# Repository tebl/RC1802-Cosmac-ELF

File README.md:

# RC1802 Cosmac ELF
There are two ways you can get involved with computers on the nonprofessional level. You can buy one of several reasonably priced hobby computers, with all the added bells and whistles you'd ever want. On the other hand, you can build your own inexpensive system from scratch.

That was rougly the start of the iconic Cosmac ELF-computers history, it was august 1976 and Popular Electronics magazine had just printed the first in a series of tutorials on how everyone could build their own computers using only common parts and the new 1802 processor from RCA.

Back in 2018 this computer still continues to fascinate... several people, definitively me among them so thanks to the glory of the Internet we can still read the original articles online at [American Radio History.Com](https://www.americanradiohistory.com/Popular-Electronics-Guide.htm):
- [1976-08 Build the Cosmac "ELF" Part 1](https://www.americanradiohistory.com/Archive-Poptronics/70s/1976/Poptronics-1976-08.pdf)
- [1976-09 Build the Cosmac "ELF" Part 2](https://www.americanradiohistory.com/Archive-Poptronics/70s/1976/Poptronics-1976-09.pdf)
- [1977-03 How to expand memory, plus more programs](https://www.americanradiohistory.com/Archive-Poptronics/70s/1977/Poptronics-1977-03.pdf)
- [1977-07 Build the PIXIE Graphic Display](https://www.americanradiohistory.com/Archive-Poptronics/70s/1977/Poptronics-1977-07.pdf)

Thankfully someone already made a version of the computer that's available in kit form and in all ways a fantastic piece of kit, that kit is [Lee Hart's 1802 Membership card](http://www.sunrise-ev.com/membershipcard.htm). If you want the whole package, that's the one to get! So, why on earth did I make another one?

Because I wanted the experience on creating one the old fashioned way, also it had a lot of bits and bobs I never could figure out how worked... I don't have a degree in electronics, so every attempt to explain it to me has so far failed so this was my attempt to reduce all the things I didn't understand to just the minimal number of things I don't understand, yet somehow the thing actually works after only five revisions! There were some stupid mistakes done on the first ones, so let's not dig too far back in the commit logs as I'm easily embarrassed.

While the first version had 256 bytes of RAM, this one supports a whopping 64K of addressable memory in the form of two slots that'll take either RAM or ROM! Should be more than enough for anyone, even if you've got ninja skills at toggling in data! Other added features includes extra blinking LEDs, a lot of them!

## Errata
- UI module revision D had issues where some traces were moved without doing ground plane refill, some lines may appear shorted because of it is. Recommended to replace UI module, but can be cut and rewired according to updated board - see [before](https://github.com/tebl/RC1802-Cosmac-ELF/raw/master/Gallery/1802_ui_d1.PNG) and [after](https://github.com/tebl/RC1802-Cosmac-ELF/raw/master/Gallery/1802_ui_d2.PNG) for reference.
- CPU module revisions D through E had a fault relating to connection of 1802 pin 37 (DMA OUT), mainly that it was never actually connected to anything. Revision F fixes this issue, but you can fix earlier revisions by adding a wire between the bottom of resistor R2 and 1802 pin 37.
- CPU module revision D had **a short** between **GND and VCC**! Later revisions do not have this issue, but if you have this version of the board: please remove pin 40 of the UI connector (top left pin) before attempting to power it up!

## Modules
In order to create a working RC1802 Cosmac ELF computer you will need the following set of modules:
- [CPU Board](https://github.com/tebl/RC1802-Cosmac-ELF/tree/master/RC1802%20CPU) ([order](https://www.pcbway.com/project/shareproject/RC1802_Cosmac_ELF__CPU_module_revision_E_.html?inviteid=88707))
- [User Interface](https://github.com/tebl/RC1802-Cosmac-ELF/tree/master/RC1802%20UI) ([order](https://www.pcbway.com/project/shareproject/RC1802_Cosmac_ELF__UI_module_revision_E_.html?inviteid=88707))

Optional modules:
- [Backplane](https://github.com/tebl/RC6502-Apple-1-Replica/tree/master/RC6502%20Backplane) ([order](https://www.pcbway.com/project/shareproject/RC6502_Apple_1_Replica__Backplane_module_revision_A_.html?inviteid=88707))

If you would like to have a copy of one or more modules, what you'll need to do is zip up the contents of the export directory for each module and give that to your favourite PCB fabrication plant. Personally I prefer to use [PCBWay](https://www.pcbway.com/setinvite.aspx?inviteid=88707), each module is only 5$ each and new accounts even get the first one free! Please use the supplied link when signing up to help me support this project, I'll get a small discount on future orders and hopefully I can afford to keep developing new and exciting modules. Even easier, you can just click the orderring-url after each of the modules - that way you'll get something that works on the first try, and you'll support me in a small way for using the URL!

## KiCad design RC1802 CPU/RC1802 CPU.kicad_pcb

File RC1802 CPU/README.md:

# RC1802 CPU Module

Of the two main modules needed for the RC1802 Cosmac ELF computer, this is the main board that includes the RCA 1802 processor along with any RAM and ROM you want. In other words this is the brains of the whole operation! In theory this board by itself should be able to function by itself though the validity of this claim is still lacking some actual testing.

# Schematic
The supplied KiCad files should be sufficient as both a schematic and as a  starting point for ordering PCBs (basically you could just zip the contents of the export folder and upload that on a fabrication site), the schematic is also available in [PDF-format](https://github.com/tebl/RC1802-Cosmac-ELF/raw/master/RC1802%20CPU/export/RC1802%20CPU.pdf) and this is what you'll need to print and work your way through this things don't work as expected after assembly.

# BOM
Most parts should be easy to get a hold of from your favourite local electronic component shop though you might have to consider other sources for the older parts such as the CPU and memory. Personally I bought most components with free shipping from China via AliExpress - prices will vary, but I found everything in larger quantities than needed for the cost of a few cups of fancy coffee! You don't need the newest and fastest components, after all it's going into a 70s-era computer so don't go overboard unless you want to (you can replace 74LS ICs with 74HCT or 74ALS if you want something newer). Most components have been produced by various manufacturers, these mostly do the same thing without any relevant differences though the choice of CPU and PIA could lead to incompatibilities so I've specified the ones I've had success with (probably also the cheapest ones available).

Some vendors will have the same ICs in different form factors, the ones you want will often be specified as being in the form of a DIP/PDIP package. Usually you'll want sockets for each of the ICs as well, a bag of assorted sockets should be easily available without setting you back more than a couple bucks. With the sockets in place, you don't need to dread having to remove an IC later, this leads to easier fault finding and you can even "borrow" them for other projects later! For the pin headers, both male and female - if you can't find the exact pin count, just buy the longer versions and snip off the parts you don't need.

Values in parenthesis is the component amounts that could be considered optional.

| Reference    | Item                                  | Count |
| ------------ | ------------------------------------- | ----- |
| PCB          | Fabricate using Gerber files ([order](https://www.pcbway.com/project/shareproject/RC1802_Cosmac_ELF__CPU_module_revision_D_.html))  |     1 |
| C1-C6        | 100nF ceramic capacitor               |     6 |
| D1-D8        | 5mm LED (assorted colours)            |   (8) |
| J5           | 1x39 right-angle pin header           |   (1) |
| J6           | 2x20 pin header                       |     1 |
| J7           | 3 pin DC barrel connector             |     1 |
| J8           | 1x05 pin header                       |     1 |
| J9           | 1x04 pin header                       |     1 |
| JP2-JP6      | 1x03 pin header                       |     5 |
| R1-R7        | 47k ohm resistor                      |     7 |
| R8-R15       | 220 ohm resistor                      |   (8) |
| U1           | 74LS04 DIP-14                         |     1 |
| U2           | CDP1802 CPU DIP-40                    |     1 |
| U3           | 74LS240 DIP-20                        |   (1) |
| U4           | 74LS373 DIP-20                        |     1 |
| U5-U6        | 62256 Static RAM DIP-28               | 1 (1) |
| X1           | 1.000Mhz TTL Oscillator, (DIP 14)     |     1 |

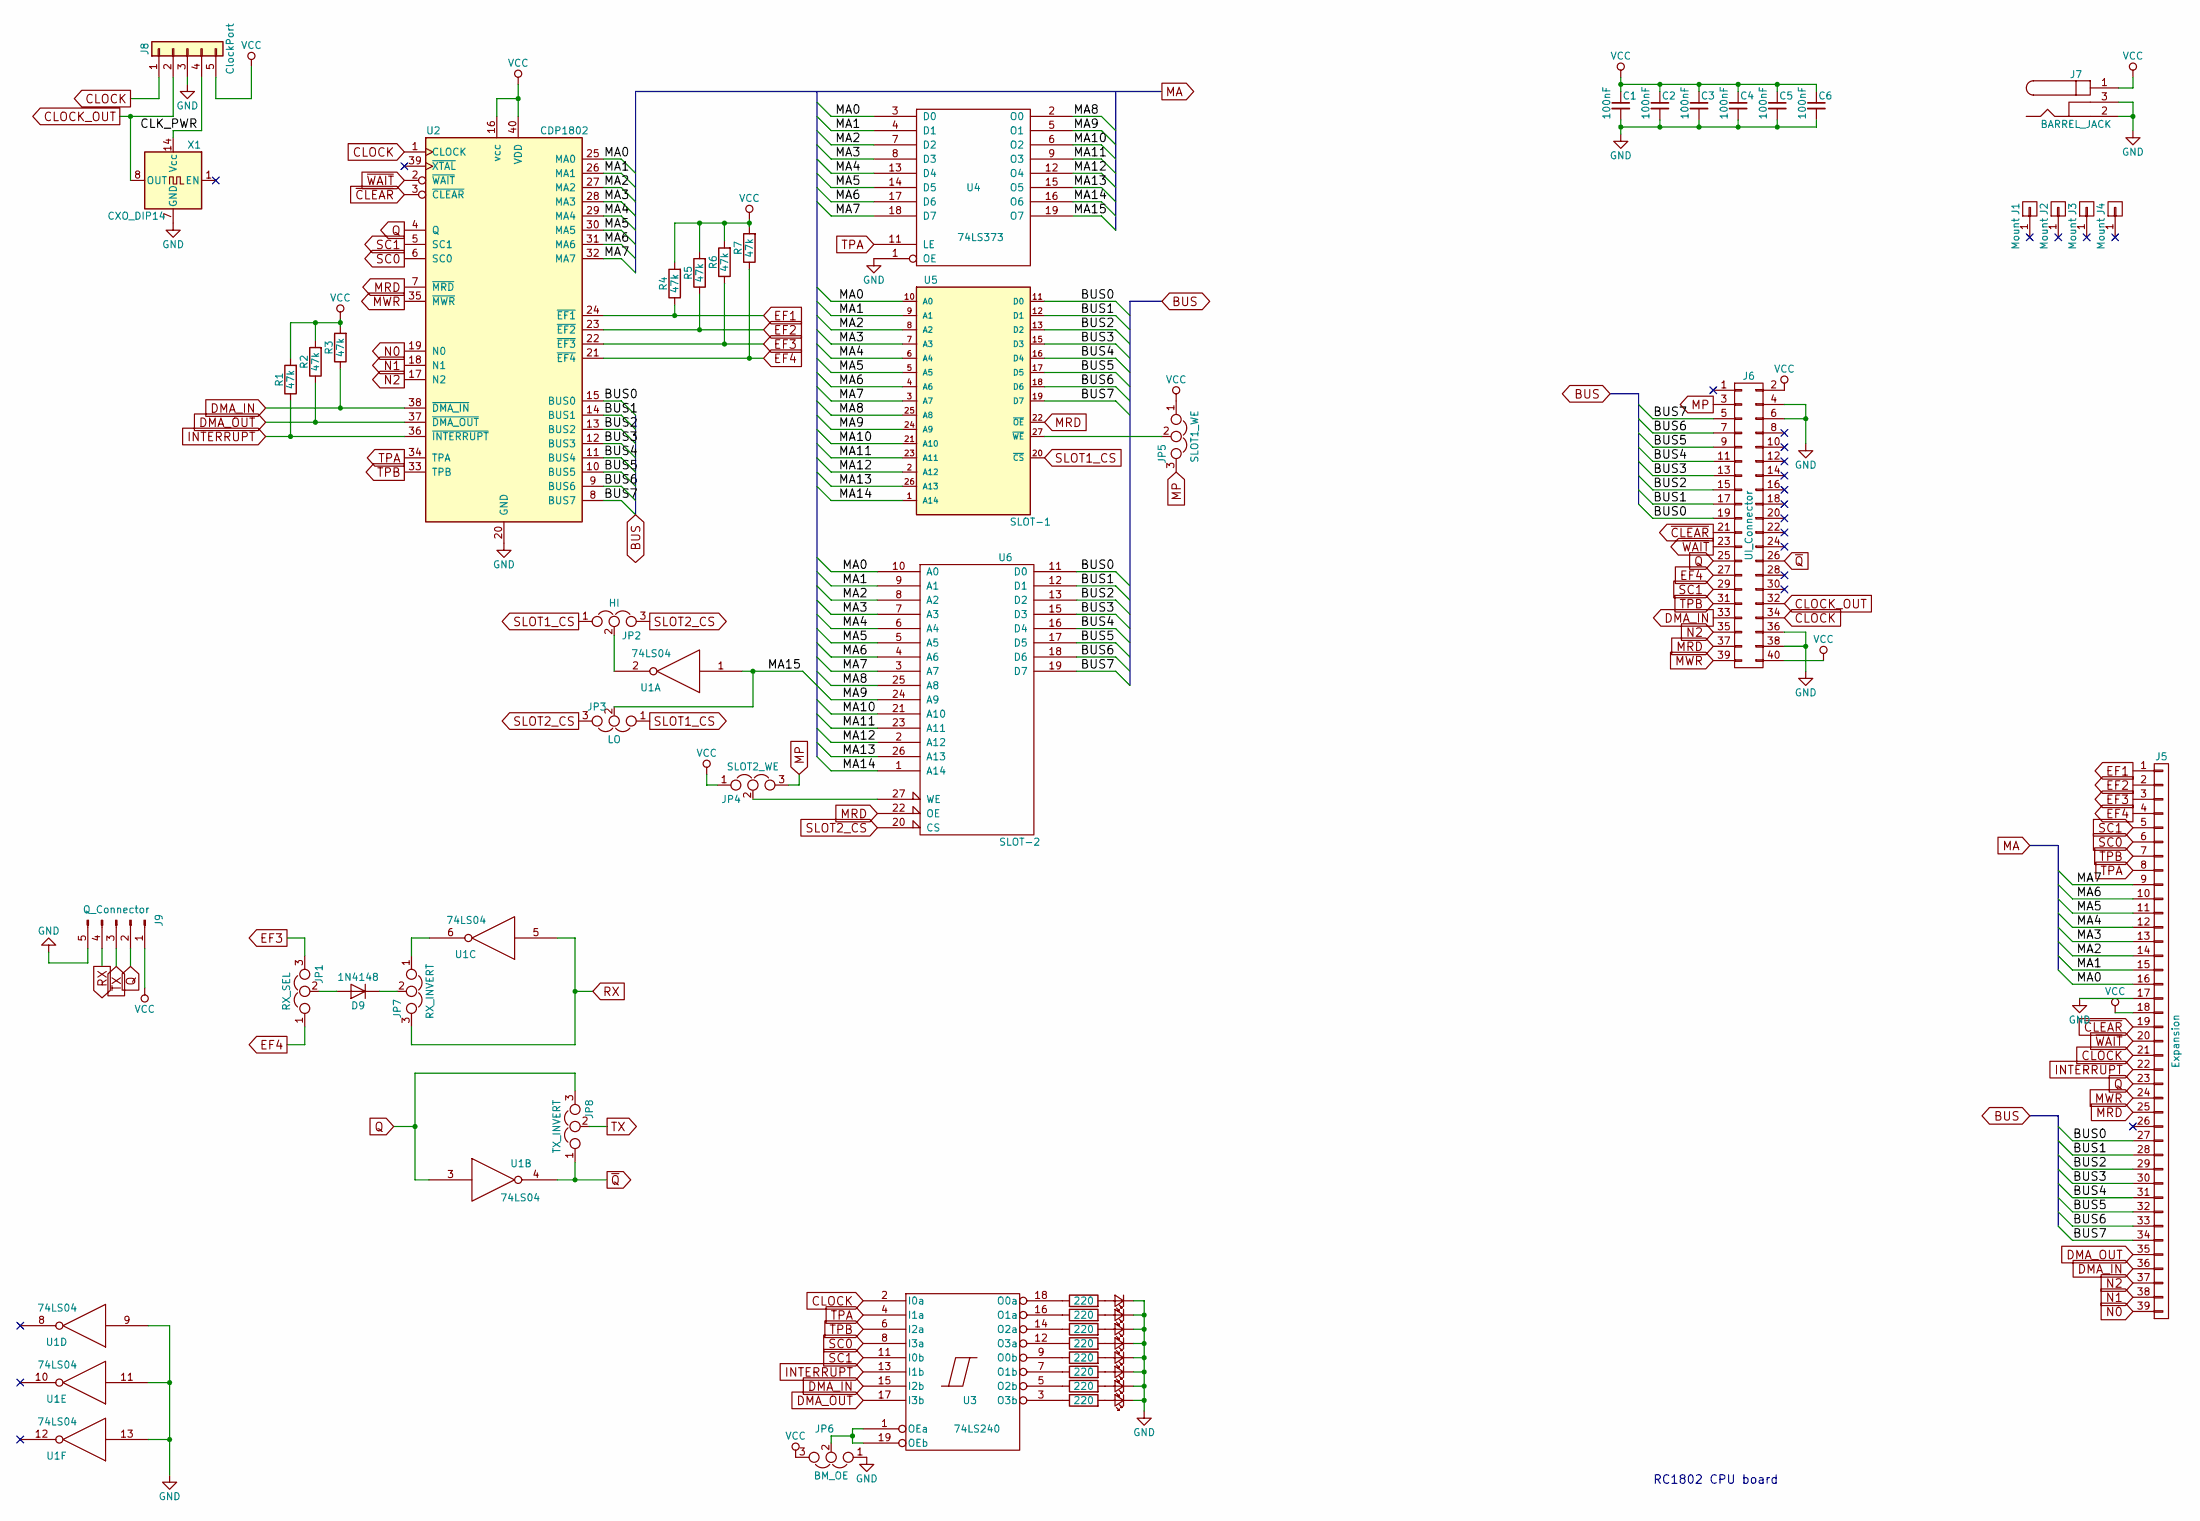
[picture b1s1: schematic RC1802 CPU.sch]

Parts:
C1, C2, C3, C4, C5, C6: 100nF; C_Disc_D4.7mm_W2.5mm_P5.00mm
D1, D2, D3, D4, D5, D6, D7, D8: LED_Small; LED_D5.0mm
D9: 1N4148; D_DO-35_SOD27_P7.62mm_Horizontal
J1, J2, J3, J4: Mount; 1pin
J5: Expansion; Pin_Header_Angled_1x39_Pitch2.54mm
J6: UI_Connector; Pin_Header_Straight_2x20_Pitch2.54mm
J7: BARREL_JACK
J8: ClockPort; Pin_Header_Straight_1x05_Pitch2.54mm
J9: Q_Connector; Pin_Header_Angled_1x05_Pitch2.54mm
JP1: RX_SEL; Pin_Header_Straight_1x03_Pitch2.54mm
JP2: HI; Pin_Header_Straight_1x03_Pitch2.54mm
JP3: LO; Pin_Header_Straight_1x03_Pitch2.54mm
JP4: SLOT2_WE; Pin_Header_Straight_1x03_Pitch2.54mm
JP5: SLOT1_WE; Pin_Header_Straight_1x03_Pitch2.54mm
JP6: BM_OE; Pin_Header_Straight_1x03_Pitch2.54mm
JP7: RX_INVERT; Pin_Header_Straight_1x03_Pitch2.54mm
JP8: TX_INVERT; Pin_Header_Straight_1x03_Pitch2.54mm
R1, R2, R3, R4, R5, R6, R7: 47k; R_Axial_DIN0207_L6.3mm_D2.5mm_P10.16mm_Horizontal
R8, R9, R10, R11, R12, R13, R14, R15: 220; R_Axial_DIN0207_L6.3mm_D2.5mm_P10.16mm_Horizontal
U1: 74LS04; DIP-14_W7.62mm_Socket
U2: CDP1802; DIP-40_W15.24mm_Socket
U3: 74LS240; DIP-20_W7.62mm_Socket
U4: 74LS373; DIP-20_W7.62mm_Socket
U5: SLOT-1; DIP-28_W15.24mm_Socket
U6: SLOT-2; DIP-28_W15.24mm_Socket
X1: CXO_DIP14; Oscillator_DIP-14

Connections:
/BUS0: J5.27, J6.19, U2.15 (BUS0), U5.11 (D0), U6.11 (D0)
/BUS1: J5.28, J6.17, U2.14 (BUS1), U5.12 (D1), U6.12 (D1)
/BUS2: J5.29, J6.15, U2.13 (BUS2), U5.13 (D2), U6.13 (D2)
/BUS3: J5.30, J6.13, U2.12 (BUS3), U5.15 (D3), U6.15 (D3)
/BUS4: J5.31, J6.11, U2.11 (BUS4), U5.16 (D4), U6.16 (D4)
/BUS5: J5.32, J6.9, U2.10 (BUS5), U5.17 (D5), U6.17 (D5)
/BUS6: J5.33, J6.7, U2.9 (BUS6), U5.18 (D6), U6.18 (D6)
/BUS7: J5.34, J6.5, U2.8 (BUS7), U5.19 (D7), U6.19 (D7)
/CLK_PWR: J8.4, X1.14 (Vcc)
/MA0: J5.16, U2.25 (MA0), U4.3 (D0), U5.10 (A0), U6.10 (A0)
/MA1: J5.15, U2.26 (MA1), U4.4 (D1), U5.9 (A1), U6.9 (A1)
/MA2: J5.14, U2.27 (MA2), U4.7 (D2), U5.8 (A2), U6.8 (A2)
/MA3: J5.13, U2.28 (MA3), U4.8 (D3), U5.7 (A3), U6.7 (A3)
/MA4: J5.12, U2.29 (MA4), U4.13 (D4), U5.6 (A4), U6.6 (A4)
/MA5: J5.11, U2.30 (MA5), U4.14 (D5), U5.5 (A5), U6.5 (A5)
/MA6: J5.10, U2.31 (MA6), U4.17 (D6), U5.4 (A6), U6.4 (A6)
/MA7: J5.9, U2.32 (MA7), U4.18 (D7), U5.3 (A7), U6.3 (A7)
/MA8: U4.2 (O0), U5.25 (A8), U6.25 (A8)
/MA9: U4.5 (O1), U5.24 (A9), U6.24 (A9)
/MA10: U4.6 (O2), U5.21 (A10), U6.21 (A10)
/MA11: U4.9 (O3), U5.23 (A11), U6.23 (A11)
/MA12: U4.12 (O4), U5.2 (A12), U6.2 (A12)
/MA13: U4.15 (O5), U5.26 (A13), U6.26 (A13)
/MA14: U4.16 (O6), U5.1 (A14), U6.1 (A14)
/MA15: JP3.2, U1.1, U4.19 (O7)
CLOCK: J5.21, J6.34, J8.1, U2.1 (CLOCK), U3.2 (I0a)
CLOCK_OUT: J6.32, J8.2, X1.8 (OUT)
DMA_IN: J5.36, J6.33, R3.1, U2.38 (~DMA_IN), U3.15 (I2b)
DMA_OUT: J5.35, R2.1, U2.37 (~DMA_OUT), U3.17 (I3b)
EF1: J5.1, R4.1, U2.24 (~EF1)
EF2: J5.2, R5.1, U2.23 (~EF2)
EF3: J5.3, JP1.3, R6.1, U2.22 (~EF3)
EF4: J5.4, J6.27, JP1.1, R7.1, U2.21 (~EF4)
GND: C1.2, C2.2, C3.2, C4.2, C5.2, C6.2, D1.1 (K), D2.1 (K), D3.1 (K), D4.1 (K), D5.1 (K), D6.1 (K), D7.1 (K), D8.1 (K), J5.17, J6.4, J6.6, J6.36, J6.38, J7.2, J7.3, J8.3, J9.5, JP6.1, U1.7 (GND), U1.9, U1.11, U1.13, U2.20 (GND), U3.10 (GND), U4.1 (OE), U4.10 (GND), U5.14 (GND), U6.14 (GND), X1.7 (GND)
INTERRUPT: J5.22, R1.1, U2.36 (~INTERRUPT), U3.13 (I1b)
MP: J6.3, JP4.3, JP5.3
MRD: J5.25, J6.37, U2.7 (~MRD), U5.22 (~OE), U6.22 (OE)
MWR: J5.24, J6.39, U2.35 (~MWR)
N0: J5.39, U2.19 (N0)
N1: J5.38, U2.18 (N1)
N2: J5.37, J6.35, U2.17 (N2)
unnamed: D1.2 (A), R8.2
unnamed: D2.2 (A), R9.2
unnamed: D3.2 (A), R10.2
unnamed: D4.2 (A), R11.2
unnamed: D5.2 (A), R12.2
unnamed: D6.2 (A), R13.2
unnamed: D7.2 (A), R14.2
unnamed: D8.2 (A), R15.2
unnamed: D9.1 (K), JP7.2
unnamed: D9.2 (A), JP1.2
unnamed: JP2.2, U1.2
unnamed: JP4.2, U6.27 (WE)
unnamed: JP5.2, U5.27 (~WE)
unnamed: JP6.2, U3.1 (OEa), U3.19 (OEb)
unnamed: JP7.1, U1.6
unnamed: R8.1, U3.18 (O0a)
unnamed: R9.1, U3.16 (O1a)
unnamed: R10.1, U3.14 (O2a)
unnamed: R11.1, U3.12 (O3a)
unnamed: R12.1, U3.9 (O0b)
unnamed: R13.1, U3.7 (O1b)
unnamed: R14.1, U3.5 (O2b)
unnamed: R15.1, U3.3 (O3b)
Q: J5.23, J6.25, J9.2, JP8.3, U1.3, U2.4 (Q)
RX: J9.4, JP7.3, U1.5
SC0: J5.6, U2.6 (SC0), U3.8 (I3a)
SC1: J5.5, J6.29, U2.5 (SC1), U3.11 (I0b)
SLOT1_CS: JP2.1, JP3.1, U5.20 (~CS)
SLOT2_CS: JP2.3, JP3.3, U6.20 (CS)
TPA: J5.8, U2.34 (TPA), U3.4 (I1a), U4.11 (LE)
TPB: J5.7, J6.31, U2.33 (TPB), U3.6 (I2a)
TX: J9.3, JP8.2
VCC: C1.1, C2.1, C3.1, C4.1, C5.1, C6.1, J5.18, J6.2, J6.40, J7.1, J8.5, J9.1, JP4.1, JP5.1, JP6.3, R1.2, R2.2, R3.2, R4.2, R5.2, R6.2, R7.2, U1.14 (VCC), U2.16 (vcc), U2.40 (VDD), U3.20 (VCC), U4.20 (VCC), U5.28 (VCC), U6.28 (VCC)
~CLEAR: J5.19, J6.21, U2.3 (~CLEAR)
~Q: J6.26, JP8.1, U1.4
~WAIT: J5.20, J6.23, U2.2 (~WAIT~)

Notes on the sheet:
RC1802 CPU board

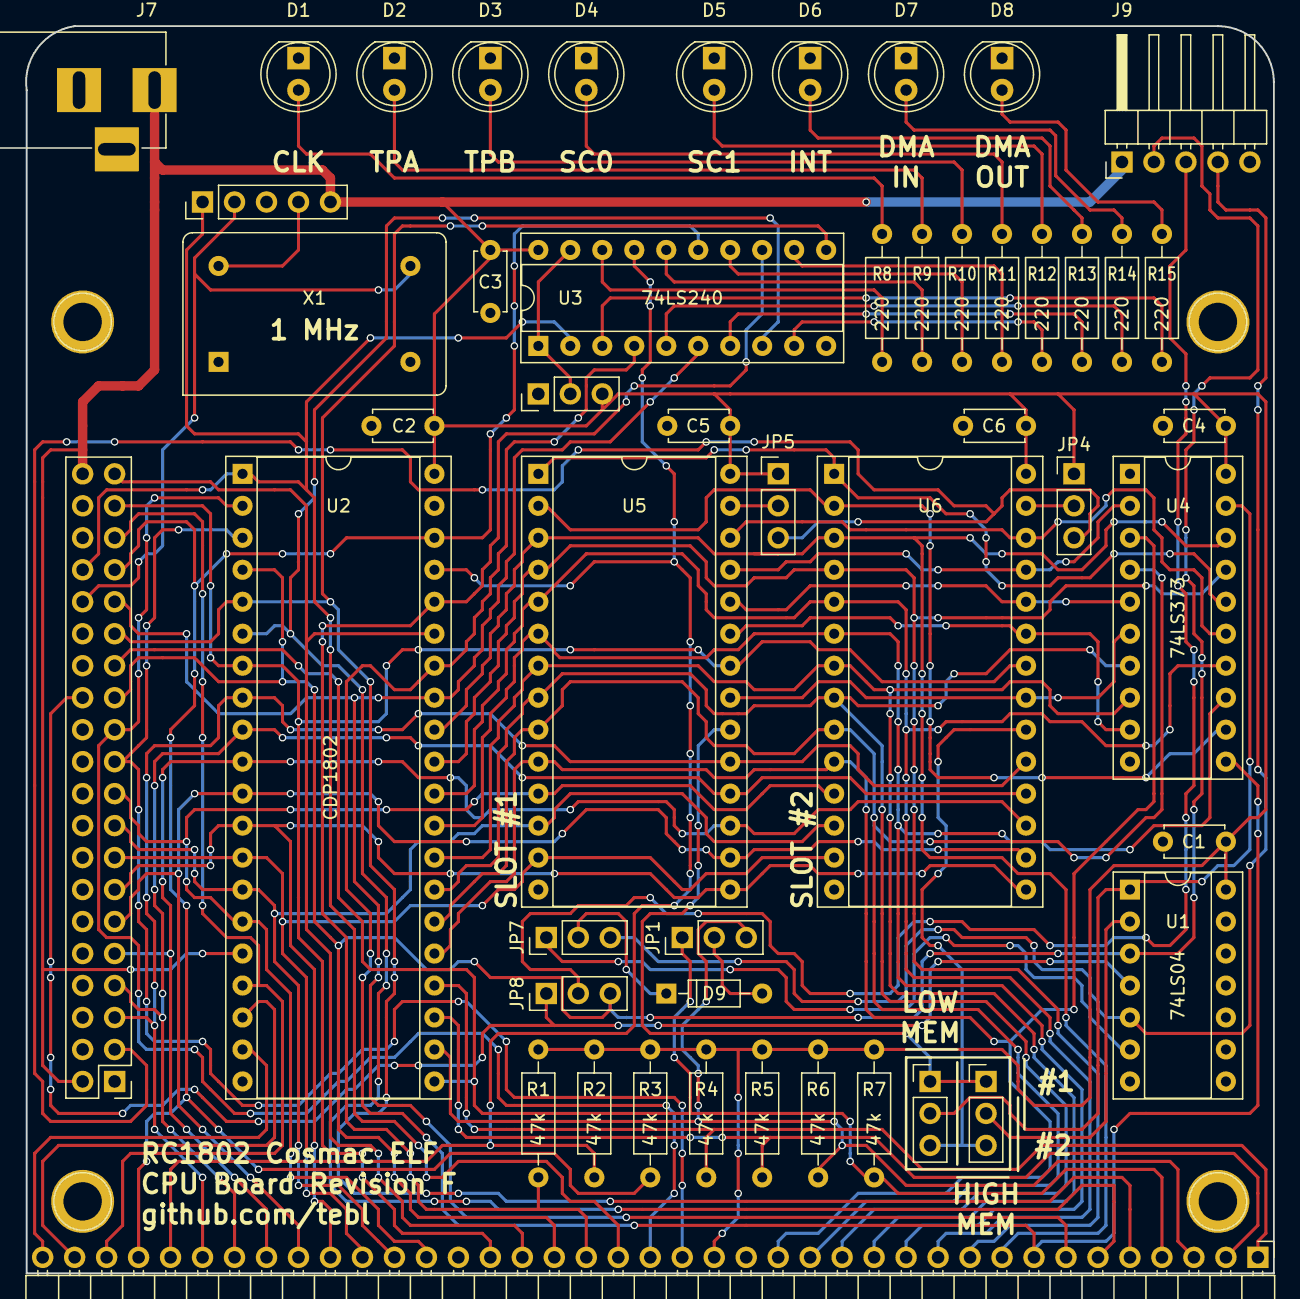
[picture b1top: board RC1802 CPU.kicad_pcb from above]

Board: 2 copper layers, 99.1 x 99.1 mm, 54 parts (0 on the bottom side), 77 nets.

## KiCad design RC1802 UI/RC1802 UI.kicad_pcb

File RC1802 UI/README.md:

# RC1802 User Interface Module

Of the two main modules needed for the RC1802 Cosmac ELF computer, this board contains all the switches you'll need to toggle in data untill you can toggle no more! Also includes the two seven segment displays used as user feedback and output.

# Schematic
The supplied KiCad files should be sufficient as both a schematic and as a  starting point for ordering PCBs (basically you could just zip the contents of the export folder and upload that on a fabrication site), the schematic is also available in [PDF-format](https://github.com/tebl/RC1802-Cosmac-ELF/raw/master/RC1802%20UI/export/RC1802%20UI.pdf) and this is what you'll need to print and work your way through this things don't work as expected after assembly.

# BOM
Most parts should be easy to get a hold of from your favourite local electronic component shop though you might have to consider other sources for the older parts such as the CPU and memory. Personally I bought most components with free shipping from China via AliExpress - prices will vary, but I found everything in larger quantities than needed for the cost of a few cups of fancy coffee! You don't need the newest and fastest components, after all it's going into a 70s-era computer so don't go overboard unless you want to (you can replace 74LS ICs with 74HCT or 74ALS if you want something newer). Most components have been produced by various manufacturers, these mostly do the same thing without any relevant differences though the choice of CPU and PIA could lead to incompatibilities so I've specified the ones I've had success with (probably also the cheapest ones available).

Some vendors will have the same ICs in different form factors, the ones you want will often be specified as being in the form of a DIP/PDIP package. Usually you'll want sockets for each of the ICs as well, a bag of assorted sockets should be easily available without setting you back more than a couple bucks. With the sockets in place, you don't need to dread having to remove an IC later, this leads to easier fault finding and you can even "borrow" them for other projects later! For the pin headers, both male and female - if you can't find the exact pin count, just buy the longer versions and snip off the parts you don't need.

Values in parenthesis is the component amounts that could be considered optional.

| Reference    | Item                                  | Count |
| ------------ | ------------------------------------- | ----- |
| PCB          | Fabricate using Gerber files ([order](https://www.pcbway.com/project/shareproject/W217819ASE8_RC1802_UI.html))  |     1 |
| C1-C7        | 100nF ceramic capacitor               |     7 |
| D1           | 5mm LED (assorted colours)            |     1 |
| D2-D7        | 1N4148 DO-35                          |     1 |
| J6           | 2x20 female pin header                |     1 |
| JP1-JP2      | 1x02 pin header                       |   (2) |
| AFF1,AFF2    | 7-segment display (common cathode)    |     2 |
| R1           | 470 ohm resistor                      |     1 |
| R2,R3        | 47k ohm resistor                      |     2 |
| R4,R5        | 330 ohm resistor                      |     2 |
| SW1, SW3-SW12| 3-pin SPDT mini toggle switch         |    11 |
| SW2          | 3-pin SPDT momentary button NO-COM-NC |     1 |
| U1           | 74LS04 DIP-14                         |     1 |
| U2           | CD4050 DIP-16                         |     1 |
| U3           | CD4013 DIP-14                         |     1 |
| U4           | 74LS10 DIP-14                         |     1 |
| U5,U7        | MC14495P1 DIP-14                      |     2 |
| U6           | 74LS244 DIP-20                        |     1 |

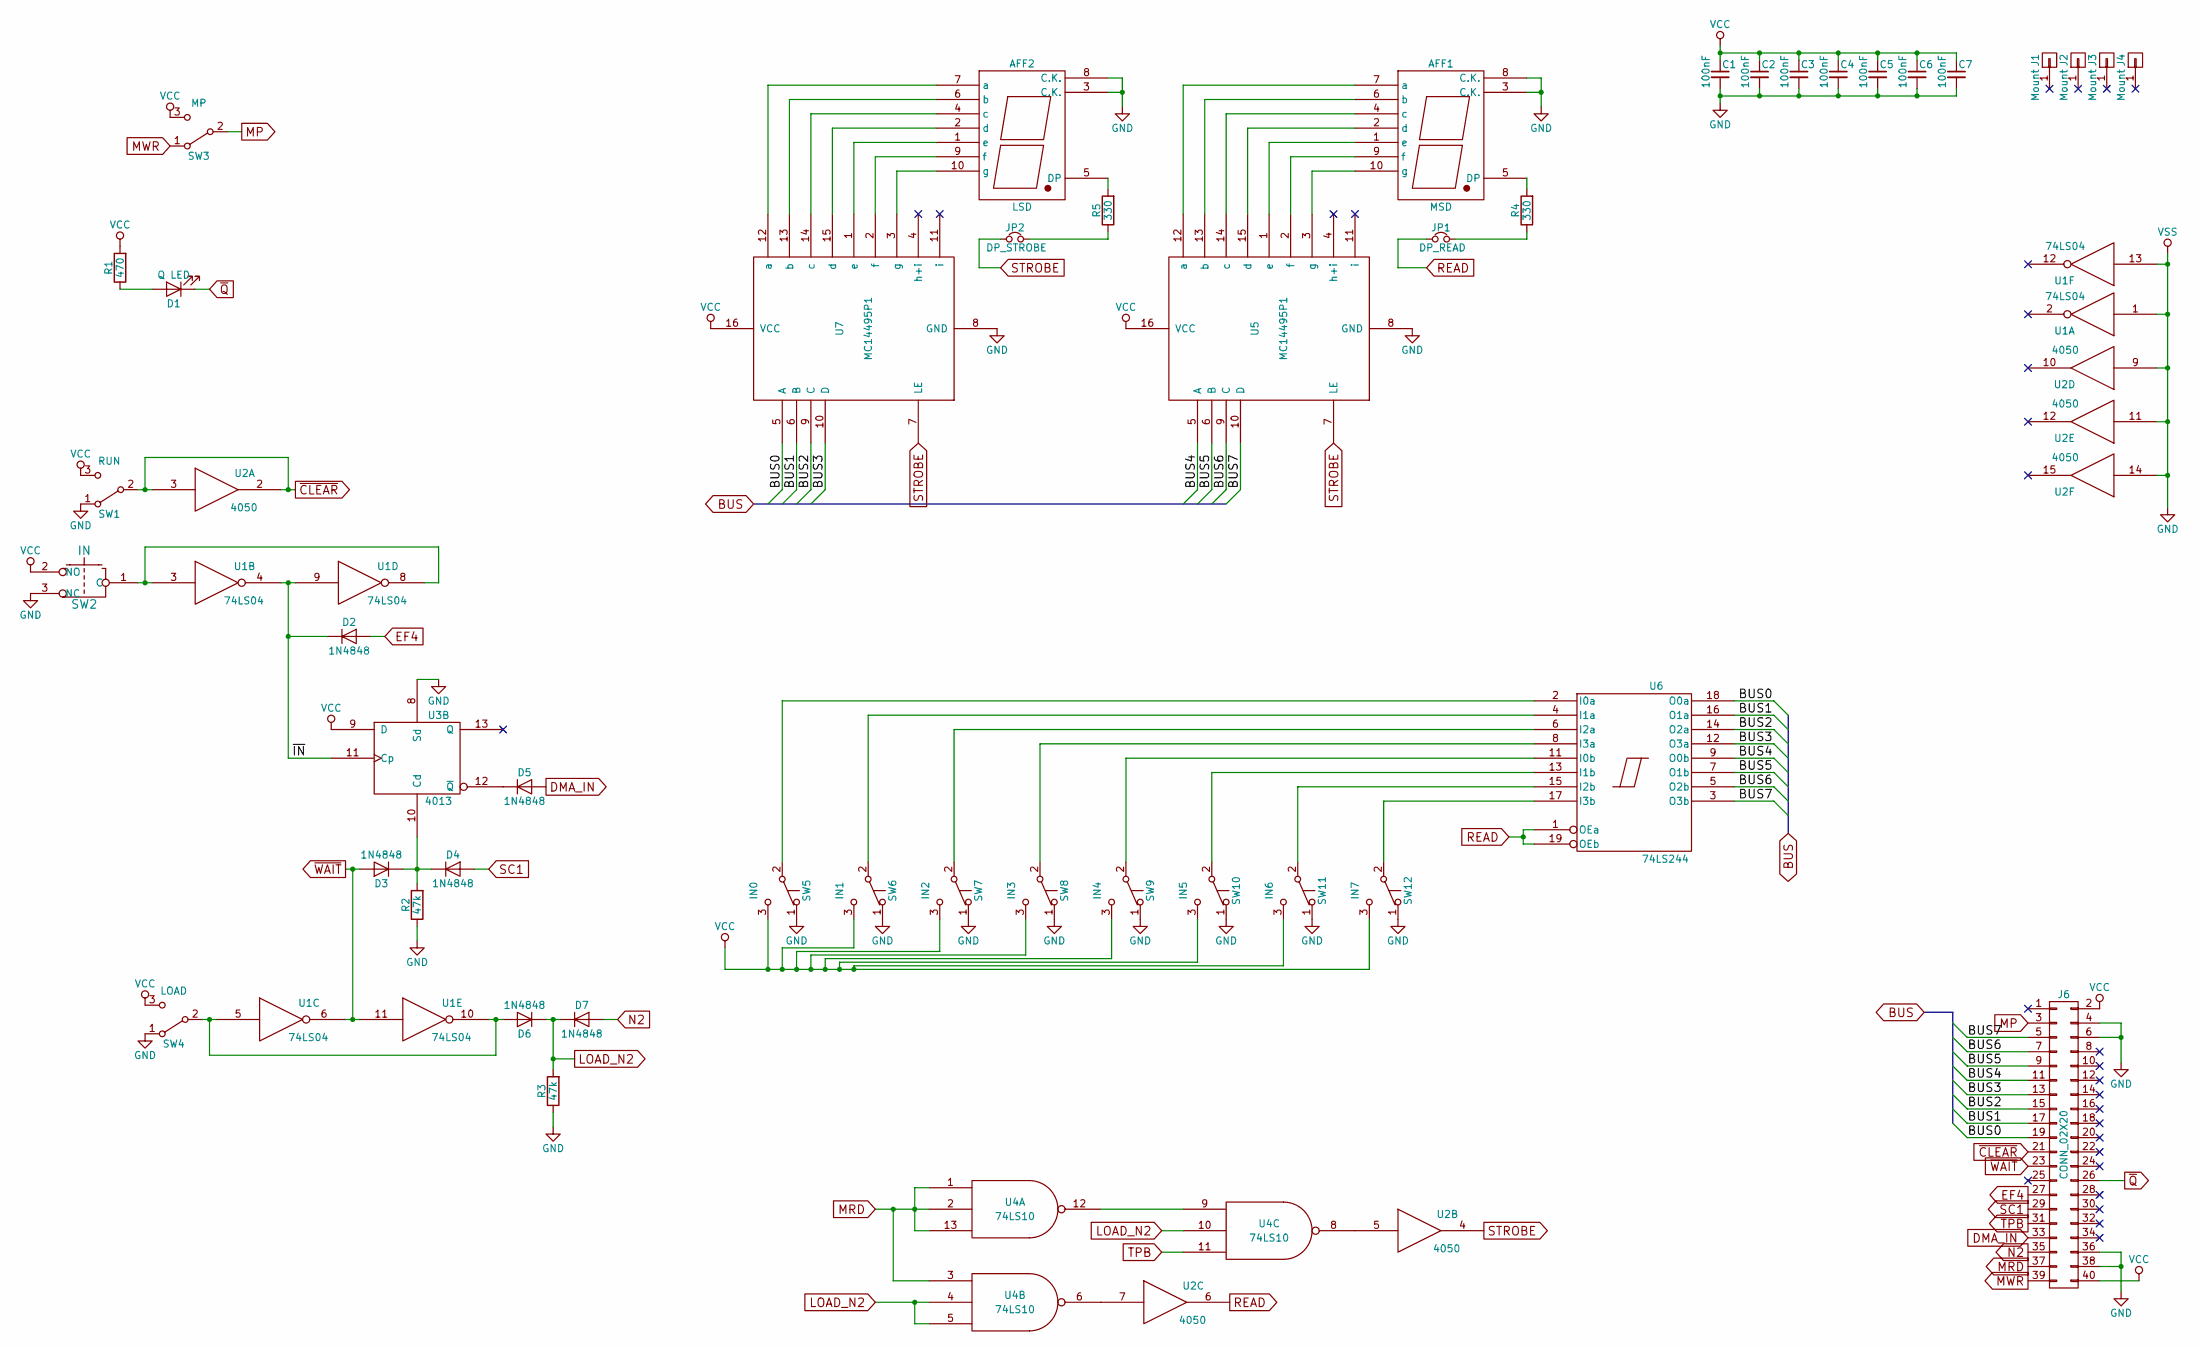
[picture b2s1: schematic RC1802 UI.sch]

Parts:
AFF1: MSD; 7SegmentLED_LTS6760_LTS6780
AFF2: LSD; 7SegmentLED_LTS6760_LTS6780
C1, C2, C3, C4, C5, C6, C7: 100nF; C_Disc_D4.7mm_W2.5mm_P5.00mm
D1: Q LED; LED_D5.0mm
D2, D3, D4, D5, D6, D7: 1N4848; D_DO-35_SOD27_P7.62mm_Horizontal
J1, J2, J3, J4: Mount; 1pin
J6: CONN_02X20; IDC_Header_Straight_40pins
JP1: DP_READ; Pin_Header_Straight_1x02_Pitch2.54mm
JP2: DP_STROBE; Pin_Header_Straight_1x02_Pitch2.54mm
R1: 470; R_Axial_DIN0207_L6.3mm_D2.5mm_P10.16mm_Horizontal
R2, R3: 47k; R_Axial_DIN0207_L6.3mm_D2.5mm_P10.16mm_Horizontal
R4, R5: 330; R_Axial_DIN0207_L6.3mm_D2.5mm_P10.16mm_Horizontal
SW1: RUN; SPDT_SWITCH
SW2: IN; SPDT_PUSH
SW3: MP; SPDT_SWITCH
SW4: LOAD; SPDT_SWITCH
SW5: IN0; SPDT_SWITCH
SW6: IN1; SPDT_SWITCH
SW7: IN2; SPDT_SWITCH
SW8: IN3; SPDT_SWITCH
SW9: IN4; SPDT_SWITCH
SW10: IN5; SPDT_SWITCH
SW11: IN6; SPDT_SWITCH
SW12: IN7; SPDT_SWITCH
U1: 74LS04; DIP-14_W7.62mm_Socket
U2: 4050; DIP-16_W7.62mm_Socket
U3: 4013; DIP-14_W7.62mm_Socket
U4: 74LS10; DIP-14_W7.62mm_Socket
U5, U7: MC14495P1; DIP-16_W7.62mm_Socket
U6: 74LS244; DIP-20_W7.62mm_Socket

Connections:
/BUS0: J6.19, U6.18 (O0a), U7.5 (A)
/BUS1: J6.17, U6.16 (O1a), U7.6 (B)
/BUS2: J6.15, U6.14 (O2a), U7.9 (C)
/BUS3: J6.13, U6.12 (O3a), U7.10 (D)
/BUS4: J6.11, U5.5 (A), U6.9 (O0b)
/BUS5: J6.9, U5.6 (B), U6.7 (O1b)
/BUS6: J6.7, U5.9 (C), U6.5 (O2b)
/BUS7: J6.5, U5.10 (D), U6.3 (O3b)
/~IN: D2.1 (K), U1.4, U1.9, U3.11 (Cp)
DMA_IN: D5.2 (A), J6.33
EF4: D2.2 (A), J6.27
GND: AFF1.3 (C.K.), AFF1.8 (C.K.), AFF2.3 (C.K.), AFF2.8 (C.K.), C1.2, C2.2, C3.2, C4.2, C5.2, C6.2, C7.2, J6.4, J6.6, J6.36, J6.38, R2.1, R3.1, SW1.1 (A), SW2.3 (NC), SW4.1 (A), SW5.1 (A), SW6.1 (A), SW7.1 (A), SW8.1 (A), SW9.1 (A), SW10.1 (A), SW11.1 (A), SW12.1 (A), U1.1, U1.7 (GND), U1.13, U2.8 (VSS), U2.9, U2.11, U2.14, U3.7 (GND), U3.8 (Sd), U4.7 (GND), U5.8 (GND), U6.10 (GND), U7.8 (GND)
LOAD_N2: D6.1 (K), D7.1 (K), R3.2, U4.4, U4.5, U4.10
MP: J6.3, SW3.2 (B)
MRD: J6.37, U4.1, U4.2, U4.3, U4.13
MWR: J6.39, SW3.1 (A)
N2: D7.2 (A), J6.35
unnamed: AFF1.1 (e), U5.1 (e)
unnamed: AFF1.2 (d), U5.15 (d)
unnamed: AFF1.4 (c), U5.14 (c)
unnamed: AFF1.5 (DP), R4.2
unnamed: AFF1.6 (b), U5.13 (b)
unnamed: AFF1.7 (a), U5.12 (a)
unnamed: AFF1.9 (f), U5.2 (f)
unnamed: AFF1.10 (g), U5.3 (g)
unnamed: AFF2.1 (e), U7.1 (e)
unnamed: AFF2.2 (d), U7.15 (d)
unnamed: AFF2.4 (c), U7.14 (c)
unnamed: AFF2.5 (DP), R5.2
unnamed: AFF2.6 (b), U7.13 (b)
unnamed: AFF2.7 (a), U7.12 (a)
unnamed: AFF2.9 (f), U7.2 (f)
unnamed: AFF2.10 (g), U7.3 (g)
unnamed: D1.2 (A), R1.1
unnamed: D3.1 (K), D4.1 (K), R2.2, U3.10 (Cd)
unnamed: D5.1 (K), U3.12 (~Q)
unnamed: D6.2 (A), SW4.2 (B), U1.5, U1.10
unnamed: JP1.2, R4.1
unnamed: JP2.2, R5.1
unnamed: SW2.1 (C), U1.3, U1.8
unnamed: SW5.2 (B), U6.2 (I0a)
unnamed: SW6.2 (B), U6.4 (I1a)
unnamed: SW7.2 (B), U6.6 (I2a)
unnamed: SW8.2 (B), U6.8 (I3a)
unnamed: SW9.2 (B), U6.11 (I0b)
unnamed: SW10.2 (B), U6.13 (I1b)
unnamed: SW11.2 (B), U6.15 (I2b)
unnamed: SW12.2 (B), U6.17 (I3b)
unnamed: U2.5, U4.8
unnamed: U2.7, U4.6
unnamed: U4.9, U4.12
READ: JP1.1, U2.6, U6.1 (OEa), U6.19 (OEb)
SC1: D4.2 (A), J6.29
STROBE: JP2.1, U2.4, U5.7 (LE), U7.7 (LE)
TPB: J6.31, U4.11
VCC: C1.1, C2.1, C3.1, C4.1, C5.1, C6.1, C7.1, J6.2, J6.40, R1.2, SW1.3 (C), SW2.2 (NO), SW3.3 (C), SW4.3 (C), SW5.3 (C), SW6.3 (C), SW7.3 (C), SW8.3 (C), SW9.3 (C), SW10.3 (C), SW11.3 (C), SW12.3 (C), U1.14 (VCC), U2.1 (VCC), U3.9 (D), U3.14 (VCC), U4.14 (VCC), U5.16 (VCC), U6.20 (VCC), U7.16 (VCC)
~CLEAR: J6.21, SW1.2 (B), U2.2, U2.3
~Q: D1.1 (K), J6.26
~WAIT: D3.2 (A), J6.23, U1.6, U1.11

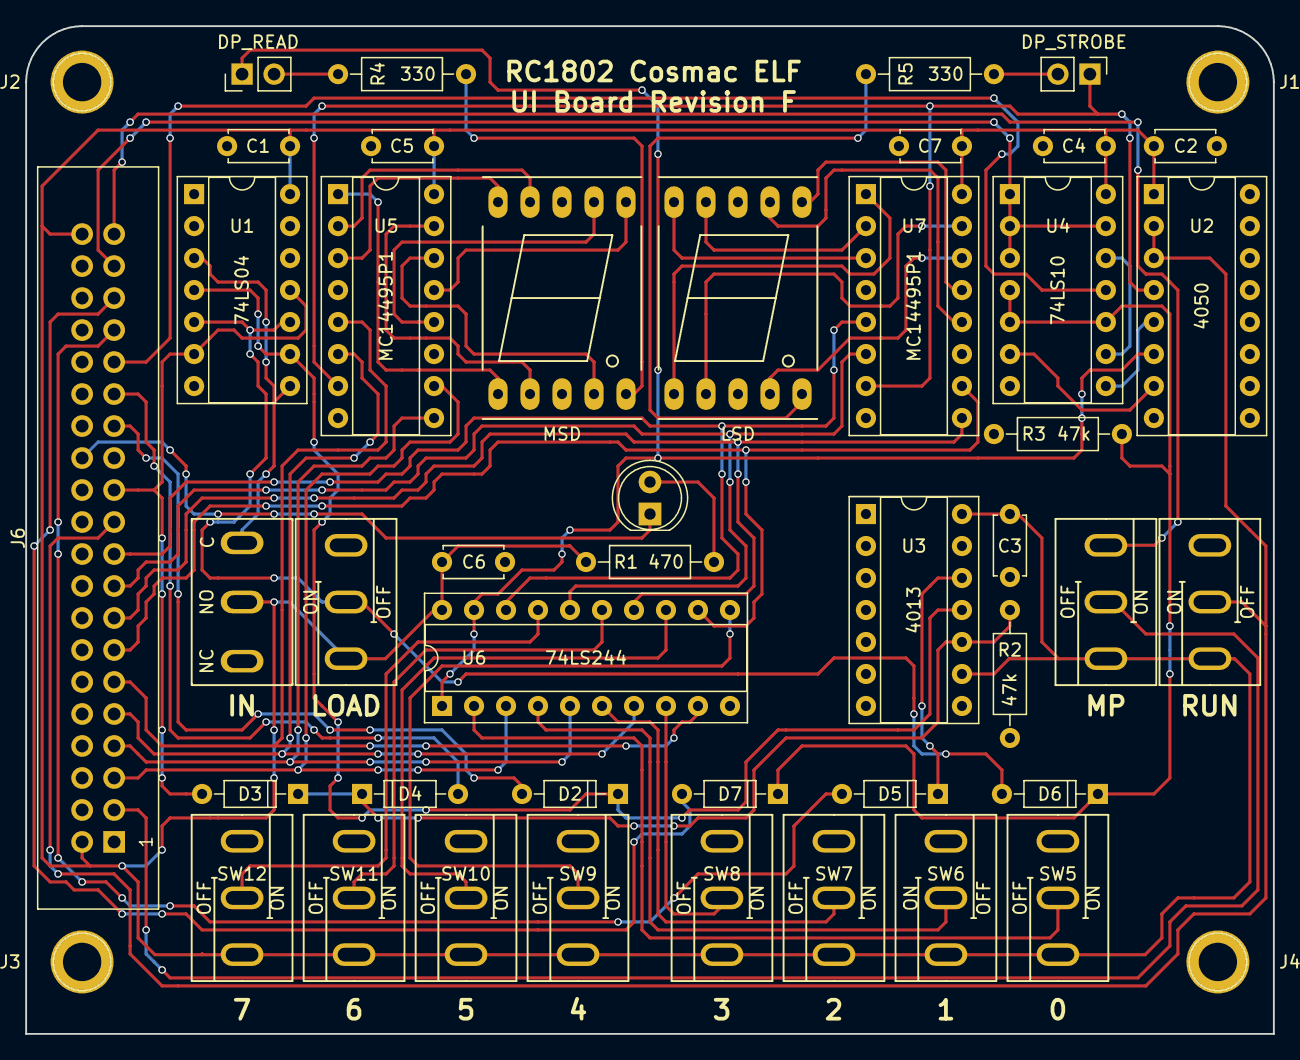
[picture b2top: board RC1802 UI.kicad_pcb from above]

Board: 2 copper layers, 99.1 x 80.0 mm, 47 parts (0 on the bottom side), 59 nets.

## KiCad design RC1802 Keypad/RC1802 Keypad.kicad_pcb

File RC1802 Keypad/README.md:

# RC1802 Keypad

Toggling in a lot of data, or even just a little bit of data using switches can be a lot of fun... and a lot of work! So in order to keep the fun going I've started experimenting with better switches, this time added the slightly bit newer method of using a hex keypad. This one sort of goes against my design principles of only using the cheapest available alternatives, but only just about by using Gateron keyboard switches instead of those tactile momentary switches. Should be fun!

Note that this is only the mechanical side of things, the logic needed will be made as a separate logic module that hopefully slots in somewhere.

# Schematic
The supplied KiCad files should be sufficient as both a schematic and as a  starting point for ordering PCBs (basically you could just zip the contents of the export folder and upload that on a fabrication site), the schematic is also available in [PDF-format](https://github.com/tebl/RC1802-Cosmac-ELF/raw/master/RC1802%20Keypad/export/RC1802%20Keypad.pdf) and this is what you'll need to print and work your way through this things don't work as expected after assembly.

# BOM
Most parts should be easy to get a hold of from your favourite local electronic component shop though you might have to consider other sources for the older parts such as the CPU and memory. Personally I bought most components with free shipping from China via AliExpress - prices will vary, but I found everything in larger quantities than needed for the cost of a few cups of fancy coffee!

For the pin headers, both male and female - if you can't find the exact pin count, just buy the longer versions and snip off the parts you don't need.

Values in parenthesis is the component amounts that could be considered optional.

| Reference    | Item                                  | Count |
| ------------ | ------------------------------------- | ----- |
| PCB          | Fabricate using Gerber files          |     1 |
| C1-C6        | 100nF ceramic capacitor               |     6 |
| J1           | 2x4 pin header                        |     1 |
|              | 2x4 pin ribbon cable                  |     1 |
| SW1-SW16     | Gateron 3 or 5 pin switches           |    16 |

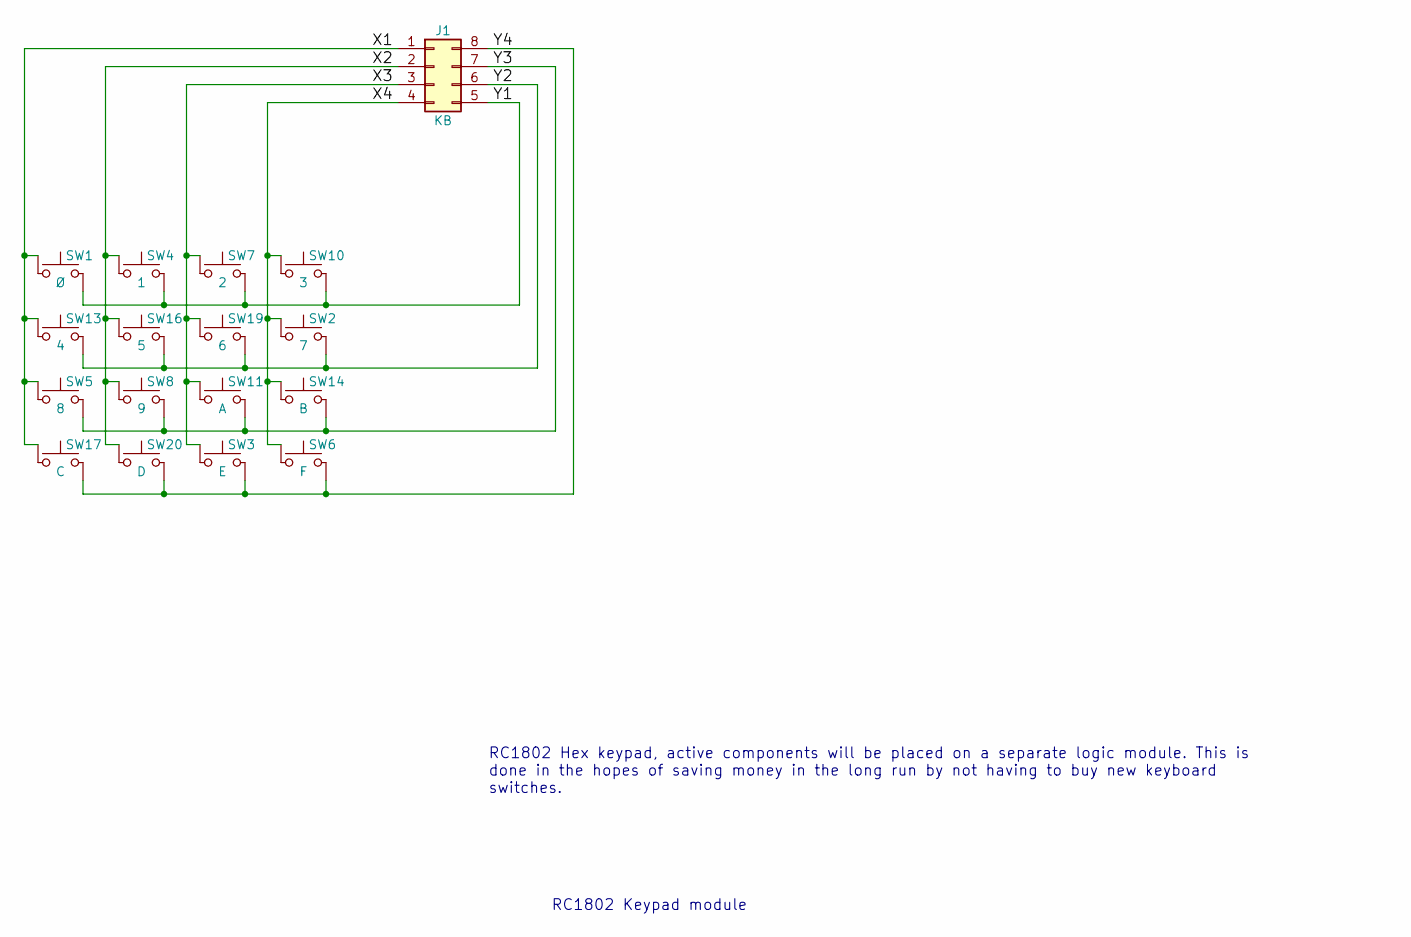
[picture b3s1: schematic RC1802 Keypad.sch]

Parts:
J1: KB; Pin_Header_Straight_2x04_Pitch2.54mm
SW1: Ø; SW_Cherry_MX_1.00u_PCB
SW2: 7; SW_Cherry_MX_1.00u_PCB
SW3: E; SW_Cherry_MX_1.00u_PCB
SW4: 1; SW_Cherry_MX_1.00u_PCB
SW5: 8; SW_Cherry_MX_1.00u_PCB
SW6: F; SW_Cherry_MX_1.00u_PCB
SW7: 2; SW_Cherry_MX_1.00u_PCB
SW8: 9; SW_Cherry_MX_1.00u_PCB
SW10: 3; SW_Cherry_MX_1.00u_PCB
SW11: A; SW_Cherry_MX_1.00u_PCB
SW13: 4; SW_Cherry_MX_1.00u_PCB
SW14: B; SW_Cherry_MX_1.00u_PCB
SW16: 5; SW_Cherry_MX_1.00u_PCB
SW17: C; SW_Cherry_MX_1.00u_PCB
SW19: 6; SW_Cherry_MX_1.00u_PCB
SW20: D; SW_Cherry_MX_1.00u_PCB

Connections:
/X1: J1.1, SW1.1, SW5.1, SW13.1, SW17.1
/X2: J1.2, SW4.1, SW8.1, SW16.1, SW20.1
/X3: J1.3, SW3.1, SW7.1, SW11.1, SW19.1
/X4: J1.4, SW2.1, SW6.1, SW10.1, SW14.1
/Y1: J1.5, SW1.2, SW4.2, SW7.2, SW10.2
/Y2: J1.6, SW2.2, SW13.2, SW16.2, SW19.2
/Y3: J1.7, SW5.2, SW8.2, SW11.2, SW14.2
/Y4: J1.8, SW3.2, SW6.2, SW17.2, SW20.2

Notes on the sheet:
RC1802 Keypad module
RC1802 Hex keypad, active components will be placed on a separate logic module. This is done in the hopes of saving money in the long run by not having to buy new keyboard switches.

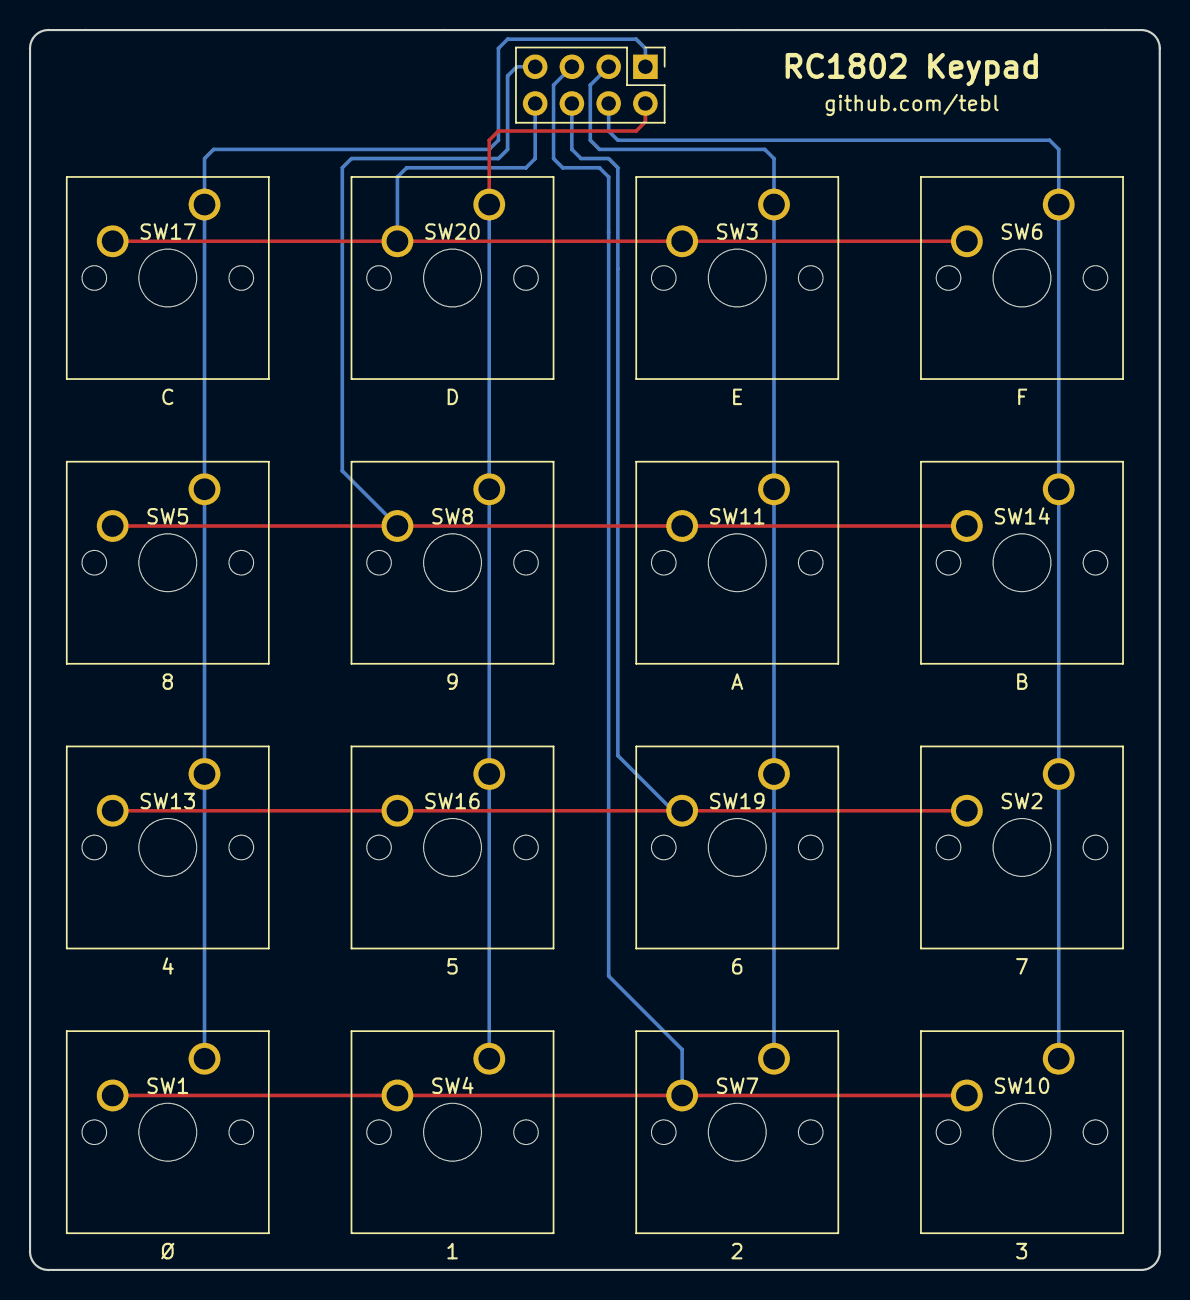
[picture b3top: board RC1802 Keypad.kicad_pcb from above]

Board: 2 copper layers, 78.1 x 85.7 mm, 17 parts (0 on the bottom side), 8 nets.
